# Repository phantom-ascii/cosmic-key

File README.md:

### (This readme.md was made by a hooman, "clankers shall not pass")

# Cosmic Key

## This is a project made by a 14 yr old nerd. Hope you like it!

## Cosmic key is a macro pad made from scratch. I designed the case the pcb and the firmware all with my smol brain, a lil bit of gpt and ***THE INTERNET***.

This project was posted on stardance: https://stardance.hackclub.com/projects/52857 go check it NOW.
This porject was also created for Hackpad. THANKS SO MUCH TO THE HACK CLUB TEAM!

Heres some eye candy:

### Feel free to rip anything out of this repo (its open source for a reason)

This project taught me alot. I now know much more about 3d modelling pcbs firmware python onshape kicad and much more than i did before and i highly recomend other people to do this project.

IDK what else to write here so thats it from me. Star the repo if you want and check out my other projects..

# BOM

## Bill of Materials

| Qty | Component                    | Description                | Source                           |
| --: | ---------------------------- | -------------------------- | -------------------------------- |
|   1 | Seeed Studio XIAO RP2040     | Main microcontroller       | Hackpad Kit                      |
|   5 | MX-style mechanical switches | 5-key input                | Hackpad Kit                      |
|   5 | 1N4148 diodes                | Key matrix (not mandatory) | Hackpad Kit                      |
|   1 | EC11 rotary encoder          | Rotary input + push switch | Hackpad Kit                      |
|   1 | Custom PCB                   | Main circuit board         | Hackpad PCB Grant                |
|   1 | 3D-printed case              | Lid + bottom case          | Hackpad / Printing Legion        |
|   4 | M3 heat-set inserts          | Case mounting              | Hackpad Kit                      |
|   4 | M3 × 16 mm screws            | Case mounting              | Hackpad Kit                      |
|   1 | Soldering iron               | PCB assembly and soldering | Hackpad $18 soldering-iron grant |

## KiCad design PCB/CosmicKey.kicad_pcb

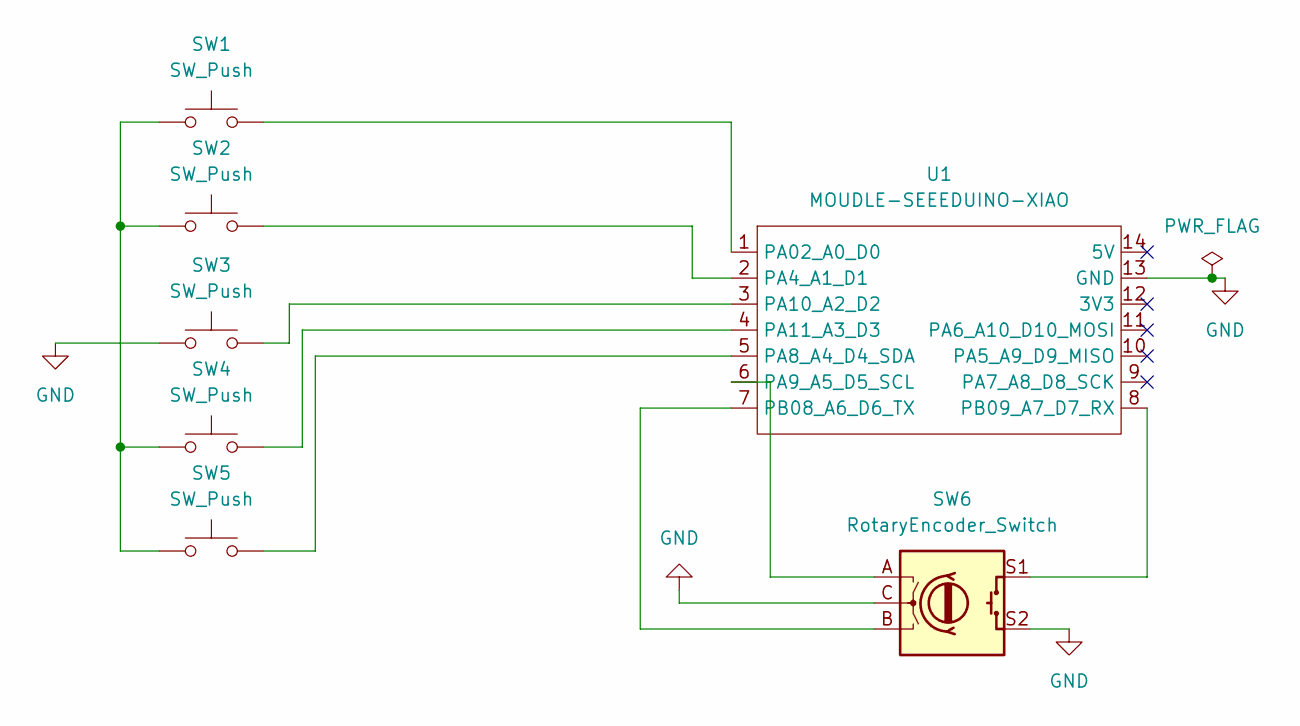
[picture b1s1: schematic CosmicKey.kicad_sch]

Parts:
SW1, SW2, SW3, SW4, SW5: SW_Push; SW_Cherry_MX_1.00u_PCB
SW6: RotaryEncoder_Switch; RotaryEncoder_Alps_EC11E-Switch_Vertical_H20mm
U1: MOUDLE-SEEEDUINO-XIAO; XIAO-Generic-Hybrid-14P-2.54-21X17.8MM

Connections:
GND: SW3.1, SW6.C, SW6.S2, U1.13 (GND)
unnamed: SW1.1, SW2.1, SW4.1, SW5.1
unnamed: SW1.2, U1.1 (PA02_A0_D0)
unnamed: SW2.2, U1.2 (PA4_A1_D1)
unnamed: SW5.2, U1.5 (PA8_A4_D4_SDA)
unnamed: SW6.A, U1.6 (PA9_A5_D5_SCL)
unnamed: SW3.2, U1.3 (PA10_A2_D2)
unnamed: SW4.2, U1.4 (PA11_A3_D3)
unnamed: SW6.B, U1.7 (PB08_A6_D6_TX)
unnamed: SW6.S1, U1.8 (PB09_A7_D7_RX)

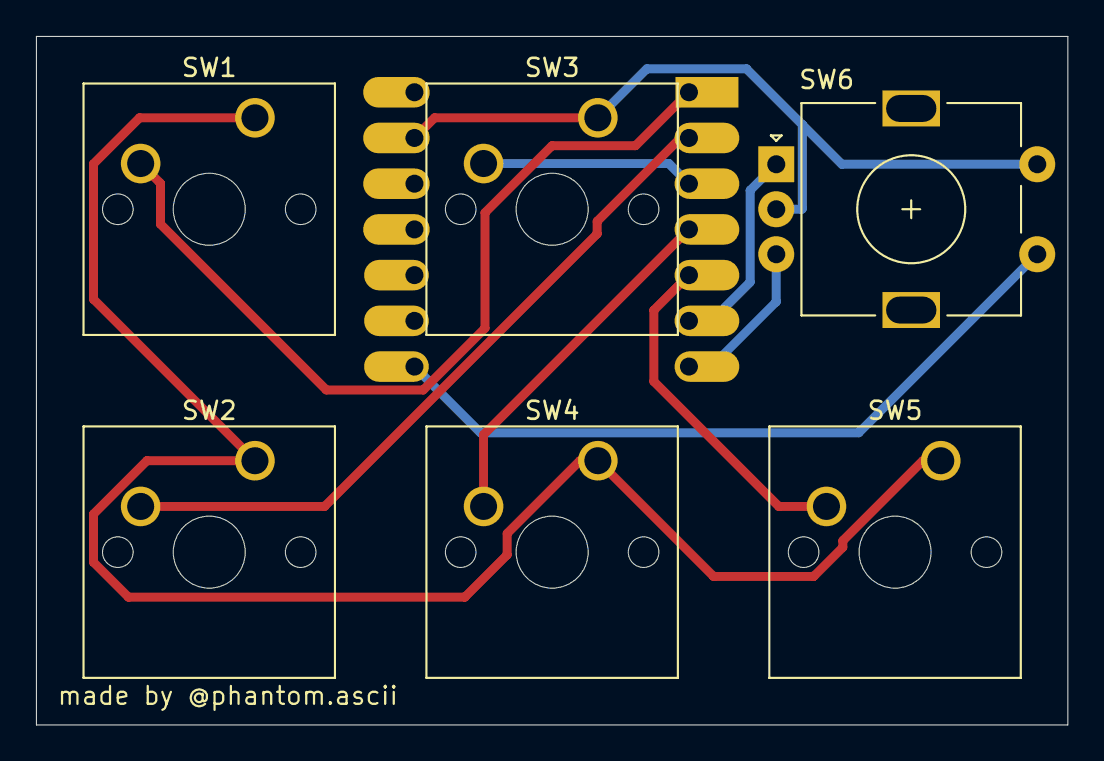
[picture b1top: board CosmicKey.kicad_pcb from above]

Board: 2 copper layers, 57.3 x 38.2 mm, 7 parts (1 on the bottom side), 10 nets.
